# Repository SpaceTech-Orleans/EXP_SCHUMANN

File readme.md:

# Schumann resonances measurement

## 

## TODO Simulation
###
Décrire tt les étages
### Suiveur
- Equation suiveur
- Simulation transient - Bode - fft
### Rauch
- Equation + fc + amplification
- Voir d'ou vient toffset
- Simulation transient - Bode - fft
### Filtre ordre 8
- equation pour fc
- simu python
Ajout opamp et role ?
### Amplification et reglage
- equation et fct biaisaga
- Simulation transient - Bode - fft
###  AOP: voir lequel, nb bits et voltage range

## Ordre:
1. Ampli sortie
2. Suiveur
3. Rauch
4. Filtre

## Ressources

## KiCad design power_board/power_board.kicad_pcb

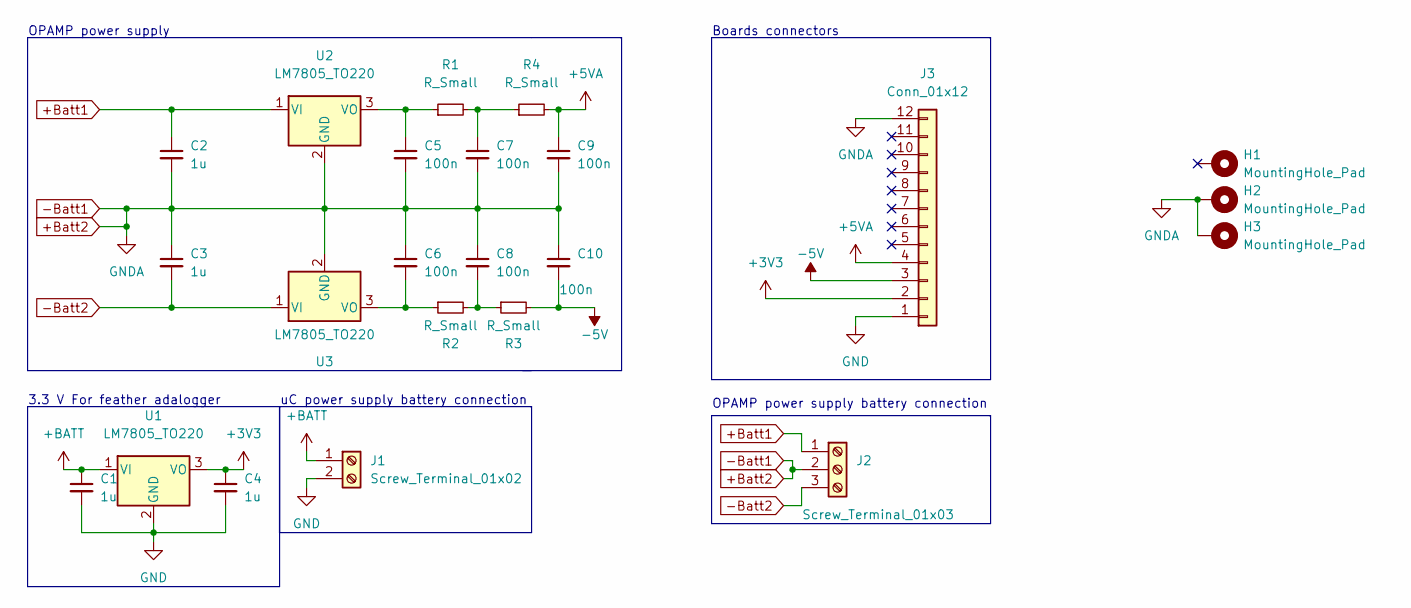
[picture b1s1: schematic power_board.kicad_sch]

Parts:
C1, C2, C3, C4: 1u; C_0805_2012Metric_Pad1.18x1.45mm_HandSolder
C5, C6, C7, C8, C9, C10: 100n; C_0805_2012Metric_Pad1.18x1.45mm_HandSolder
H1, H2, H3: MountingHole_Pad; MountingHole_3.2mm_M3_Pad_Via
J1: Screw_Terminal_01x02; TerminalBlock_bornier-2_P5.08mm
J2: Screw_Terminal_01x03; TerminalBlock_bornier-3_P5.08mm
J3: Conn_01x12; PinSocket_1x12_P2.54mm_Vertical
R1, R2, R3, R4: R_Small; R_0805_2012Metric_Pad1.20x1.40mm_HandSolder
U1, U2, U3: LM7805_TO220; TO-220-3_Horizontal_TabDown

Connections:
+3V3: C4.1, J3.2, U1.3 (VO)
+5VA: C9.1, J3.4, R4.2
+BATT: C1.1, J1.1, U1.1 (VI)
+Batt1: C2.1, J2.1, U2.1 (VI)
+Batt2: C2.2, C3.1, C5.2, C6.1, C7.2, C8.1, C9.2, C10.1, H2.1, H3.1, J2.2, J3.12, U2.2 (GND), U3.2 (GND)
-5V: C10.2, J3.3, R3.2
-Batt2: C3.2, J2.3, U3.1 (VI)
GND: C1.2, C4.2, J1.2, J3.1, U1.2 (GND)
unnamed: C5.1, R1.1, U2.3 (VO)
unnamed: C6.2, R2.1, U3.3 (VO)
unnamed: C7.1, R1.2, R4.1
unnamed: C8.2, R2.2, R3.1

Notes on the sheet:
Boards connectors
uC power supply battery connection
3.3 V For feather adalogger
OPAMP power supply
OPAMP power supply battery connection

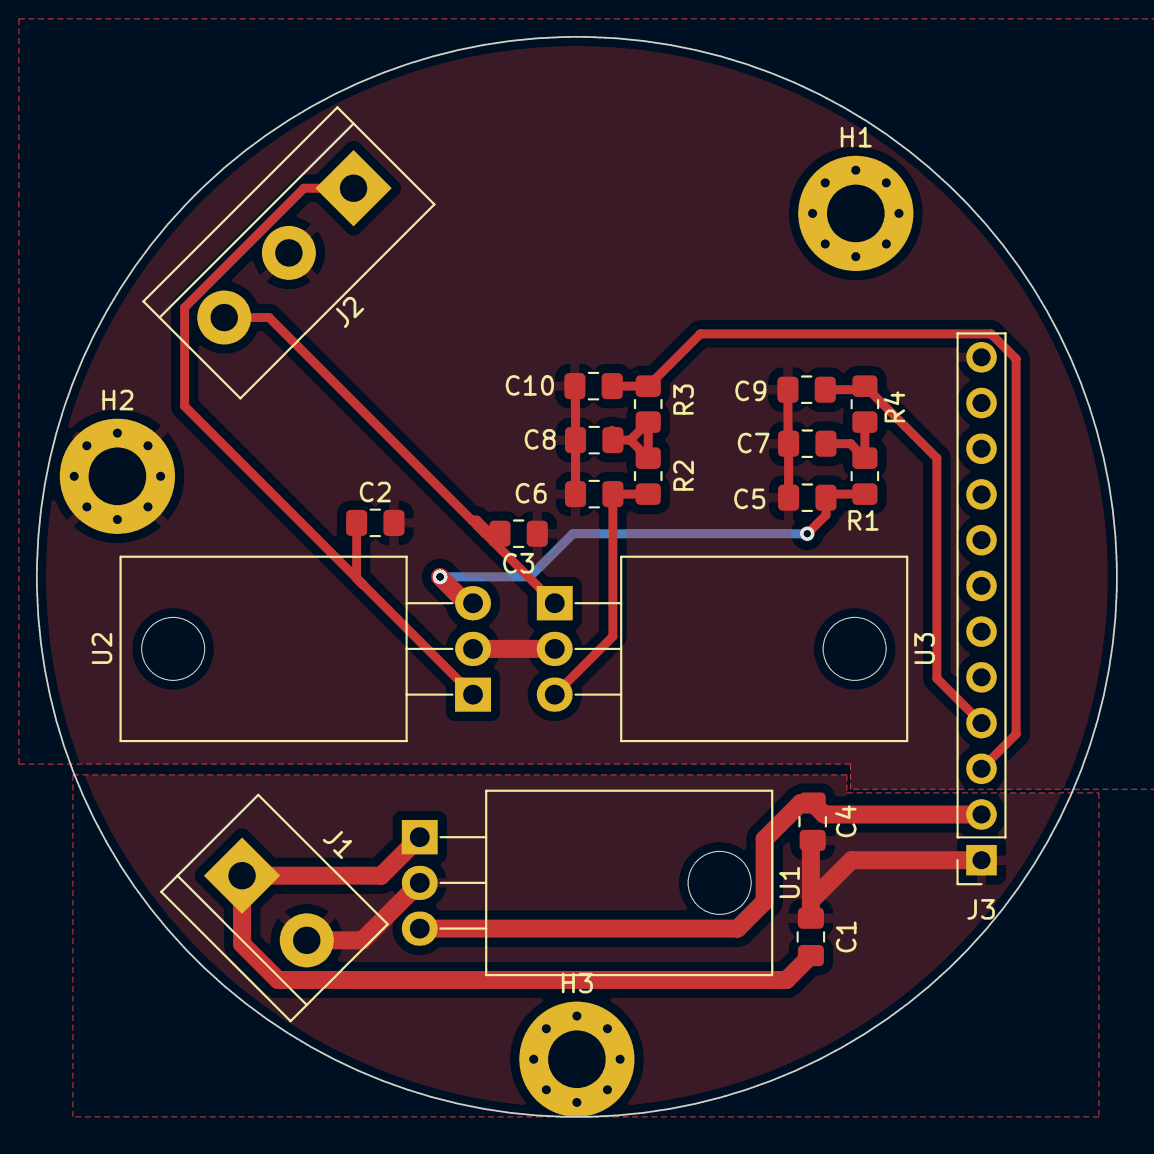
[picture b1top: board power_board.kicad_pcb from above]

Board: 2 copper layers, 60.0 x 60.0 mm, 23 parts (0 on the bottom side), 12 nets.

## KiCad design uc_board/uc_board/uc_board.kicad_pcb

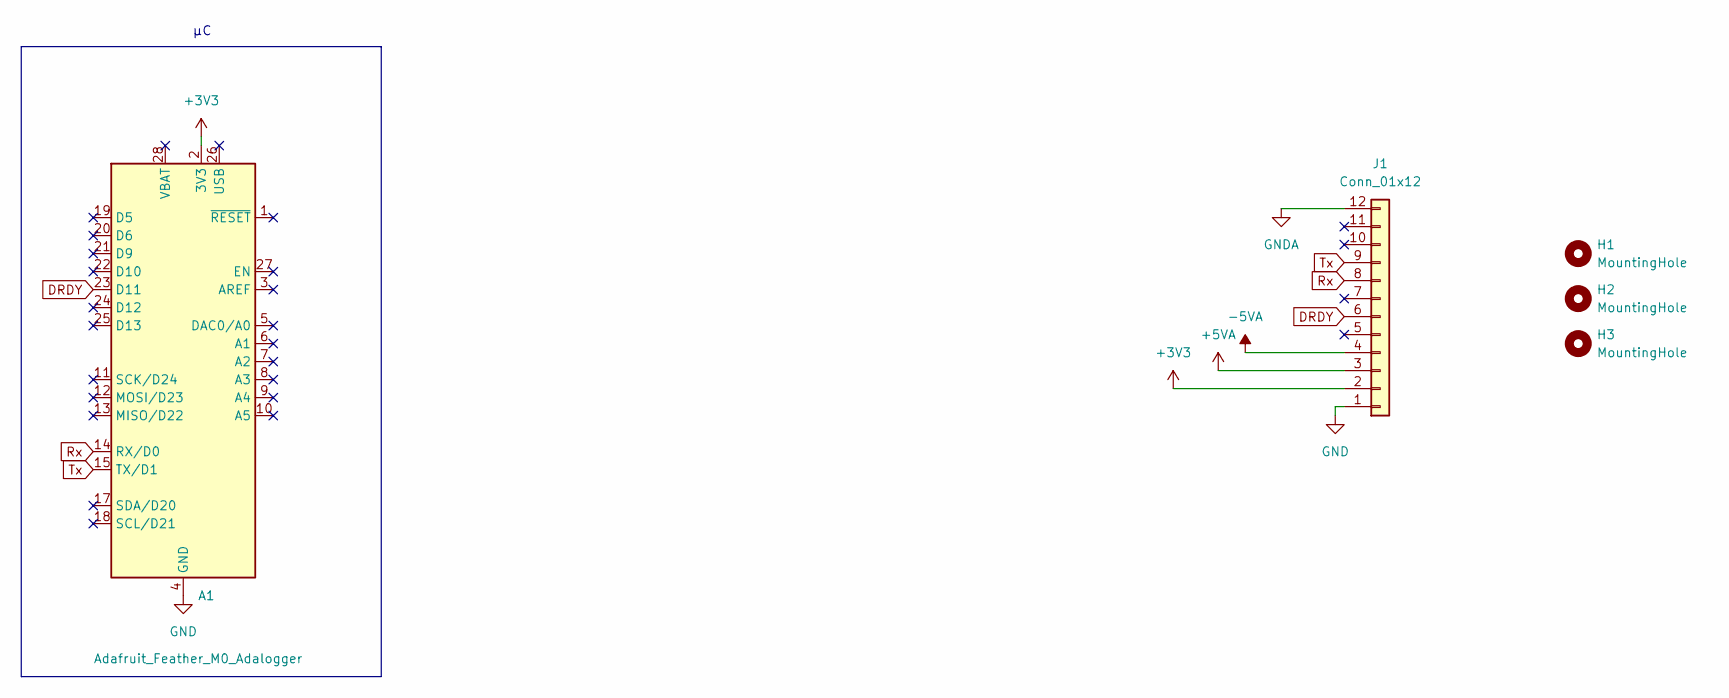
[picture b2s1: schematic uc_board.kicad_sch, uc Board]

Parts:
A1: Adafruit_Feather_M0_Adalogger; Adafruit_Feather
H1, H2, H3: MountingHole; MountingHole_3.5mm_Pad
J1: Conn_01x12; PinSocket_1x12_P2.54mm_Vertical

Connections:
+3V3: A1.2 (3V3), J1.2
+5VA: J1.3
-5VA: J1.4
DRDY: A1.23 (D11), J1.6
GND: A1.4 (GND), A1.16 (GND), J1.1
GNDA: J1.12
Rx: A1.14 (RX/D0), J1.8
Tx: A1.15 (TX/D1), J1.9

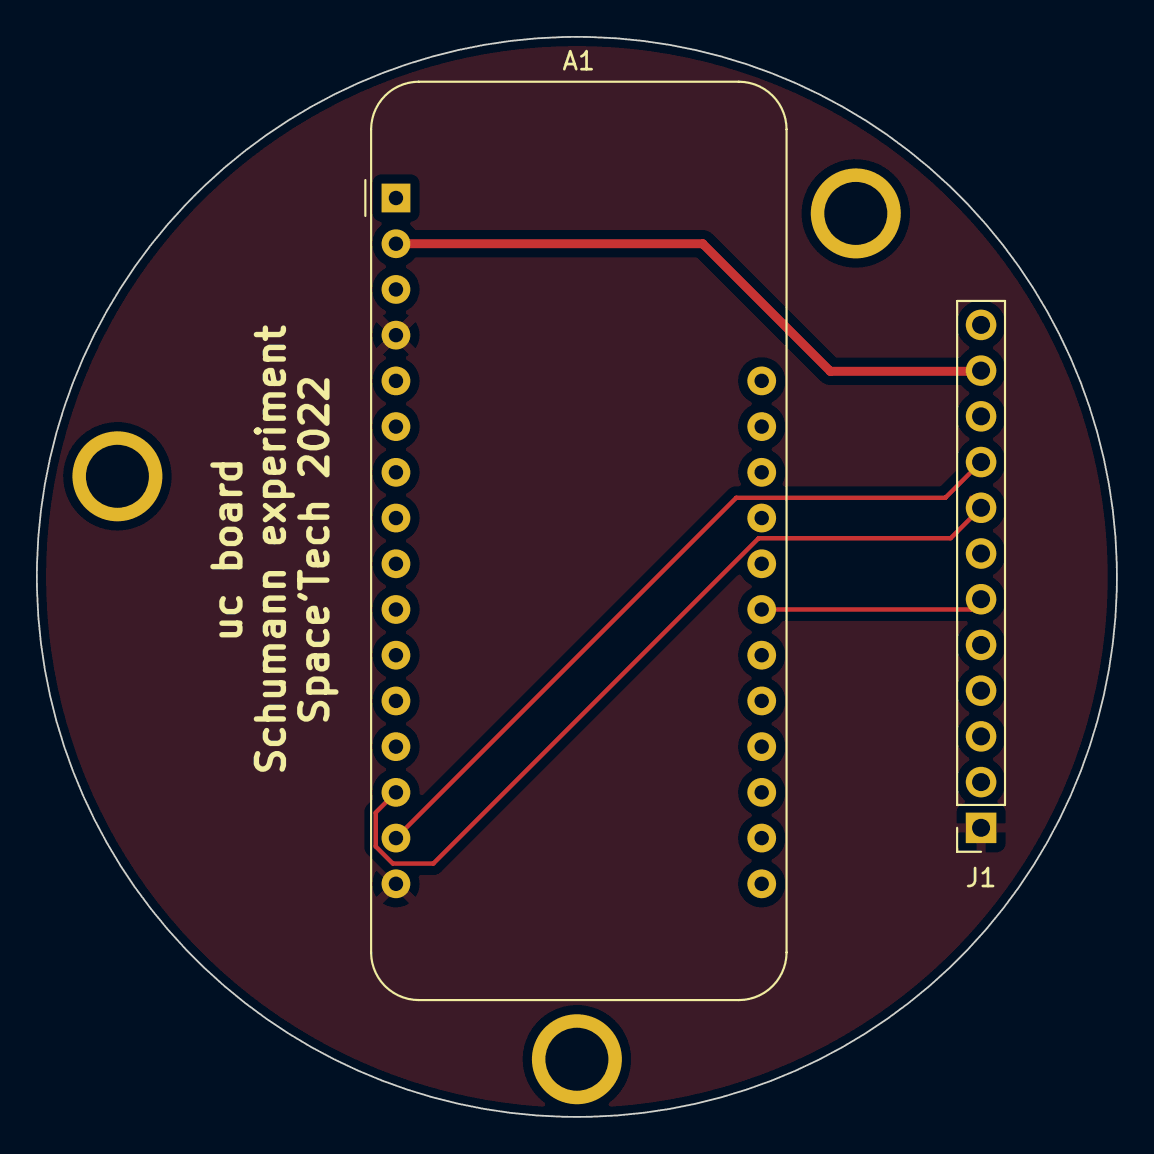
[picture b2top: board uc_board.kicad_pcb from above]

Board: 2 copper layers, 60.0 x 60.0 mm, 5 parts (0 on the bottom side), 5 nets.

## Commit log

2022-04-03 Transfert documents to new repo
2022-04-03 Experiences
2022-04-03 Change project tree
2022-04-03 Pre amp simulation ok
2022-04-03 Simulation Rauch 1 ok
2022-04-03 Add Max295CSA datasheet and rename folder
2022-04-04 Create new folder
2022-04-04 Lt spice simulation from python signal working
2022-04-04 Change signal path from absolute to relative
2022-04-15 altium
2022-04-15 update cad and mc choice to do
2022-04-16 update plans
2022-04-18 design and schematic
2022-04-18 Update python code and add amplifier to schematics
2022-05-03 Add ltspice output to wav file and read file from python
2022-05-26 add pcb
2022-05-26 update pcb
2022-06-17 Update uc_board and create power card
